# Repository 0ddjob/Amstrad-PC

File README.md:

# Amstrad PC Related Projects

## Amstrad ACL-386SX BIOS ROM
Dump of the ROM from the Amstrad ACL-386SX laptop computer.<br>
PhoenixBIOS A386 Version 1.01, dated 19-Apr-1990 (I think).<br>

## [Amstrad ACL-386SX External Floppy Adaptor](/Amstrad_ACL386_Floppy)
Small Centronics adaptor board to allow connection of a 3.5" floppy or Gotek (via IDC) or 5.25" floppy (via edge connector).<br>

### Status
11-Sep-2025: Work in progress<br>

## [Amstrad PPC XT CF-Lite](/Amstrad_PPC_Internal_Expansion)
An early attempt by an inexperienced me trying to replace the internal modem in the Amstrad PPC1512/1640 with a combination XT-IDE and CF-Lite board.<br>

It *should* work but I really need to re-visit the design (in light of several years more experience) and get this thing working!<br>

### Status
11-Sept-2025: Untested<br>

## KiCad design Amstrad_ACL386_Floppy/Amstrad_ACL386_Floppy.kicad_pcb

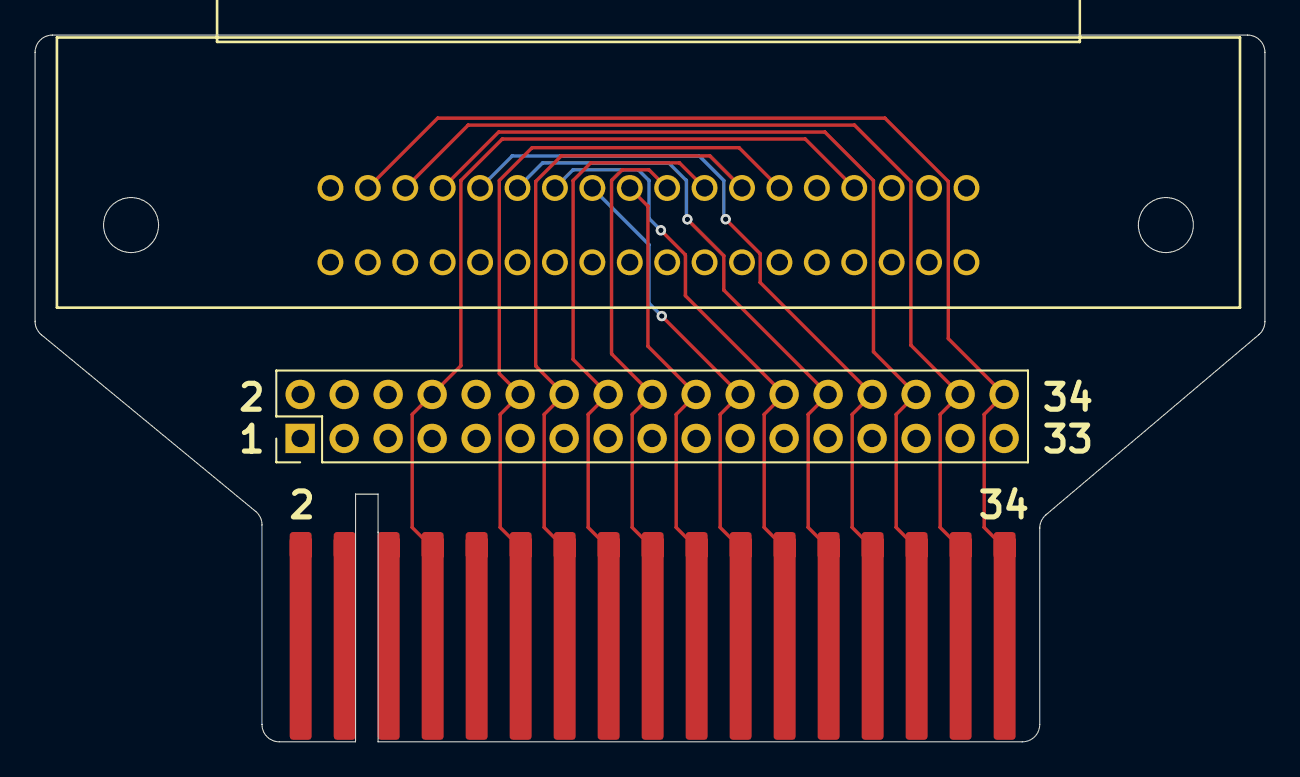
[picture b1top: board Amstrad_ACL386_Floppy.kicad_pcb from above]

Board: 2 copper layers, 71.0 x 40.8 mm, 3 parts (0 on the bottom side), 14 nets.

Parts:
J1: External Floppy; 112-036-113R001_Centronics_36way
J3: 3.5" Floppy; PinHeader_2x17_P2.54mm_Vertical
J4: 5.25" Floppy; 5.25_ Floppy Edge Connector

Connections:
DIR: J1.27, J3.18, J4.18
DSKCHG/RG: J1.35, J3.34, J4.34
GND: J1.1, J1.2, J1.3, J1.4, J1.5, J1.6, J1.7, J1.8, J1.9, J1.10, J1.11, J1.12, J1.13, J1.14, J1.15, J1.16, J1.17, J1.18, J1.36, J3.1, J3.3, J3.5, J3.7, J3.9, J3.11, J3.13, J3.15, J3.17, J3.19, J3.21, J3.23, J3.25, J3.27, J3.29, J3.31, J3.33, J4.1, J4.3, J4.5, J4.7, J4.9, J4.11, J4.13, J4.15, J4.17, J4.19, J4.21, J4.23, J4.25, J4.27, J4.29, J4.31, J4.33
HDSEL: J1.34, J3.32, J4.32
~DR0: J1.25, J3.14, J4.14
~DR1: J1.24, J3.12, J4.12
~INDEX: J1.22, J3.8, J4.8
~MTR1: J1.26, J3.16, J4.16
~RDATA: J1.33, J3.30, J4.30
~STEP: J1.28, J3.20, J4.20
~TRK0: J1.31, J3.26, J4.26
~WDATA: J1.29, J3.22, J4.22
~WGATE: J1.30, J3.24, J4.24
~WRTPRT: J1.32, J3.28, J4.28

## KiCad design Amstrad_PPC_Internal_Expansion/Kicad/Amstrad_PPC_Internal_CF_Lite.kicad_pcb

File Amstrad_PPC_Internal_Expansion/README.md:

# Amstrad PPC XT CF Lite
Internal CF interface for the Amstrad PPC512/640.<br>

Replaces the internal modem board with a combination ISA interface & XT-IDE/Compact Flash interface.<br> 

Heavily based on Sergey Kiselev's design<br>
[Github page](https://github.com/skiselev)<br>
[WWW page](http://www.malinov.com/Home/sergeys-projects/xt-cf-lite)<br>

Which is apparently a remake of James Pearce's card:<br>
[WWW page](http://www.lo-tech.co.uk/wiki/XT-CF-lite)<br>

I am using some of Sergey's Kicad symbols/footprints:<br>
[Sergey's Kicad symbols](https://github.com/skiselev/my_kicad_library)<br>

Changes requires for internal mounting in the Amstrad PPC:<br>
[1] The following signals are generated directly from the internal gate arrays and should be buffered with a non-inverting buffer (i.e. 72HC244): A00 to A07, !MEMW, !MEMR, !IOW, !IOR, RESET<br>
_(there are others but irrelevant for our purposes)_<br>
[2] The data signals (D0 to D7) are at CMOS levels and should be pulled up to TTL levels with 10KΩ resistors<br>
[3] The internal modem board we are replacing is roughly 200x120mm<br>
[4] Technically the PPC should be powered by the "expansion unit" and not the other way around ... don't tell anyone<br>

Currently untested ...<br><br>

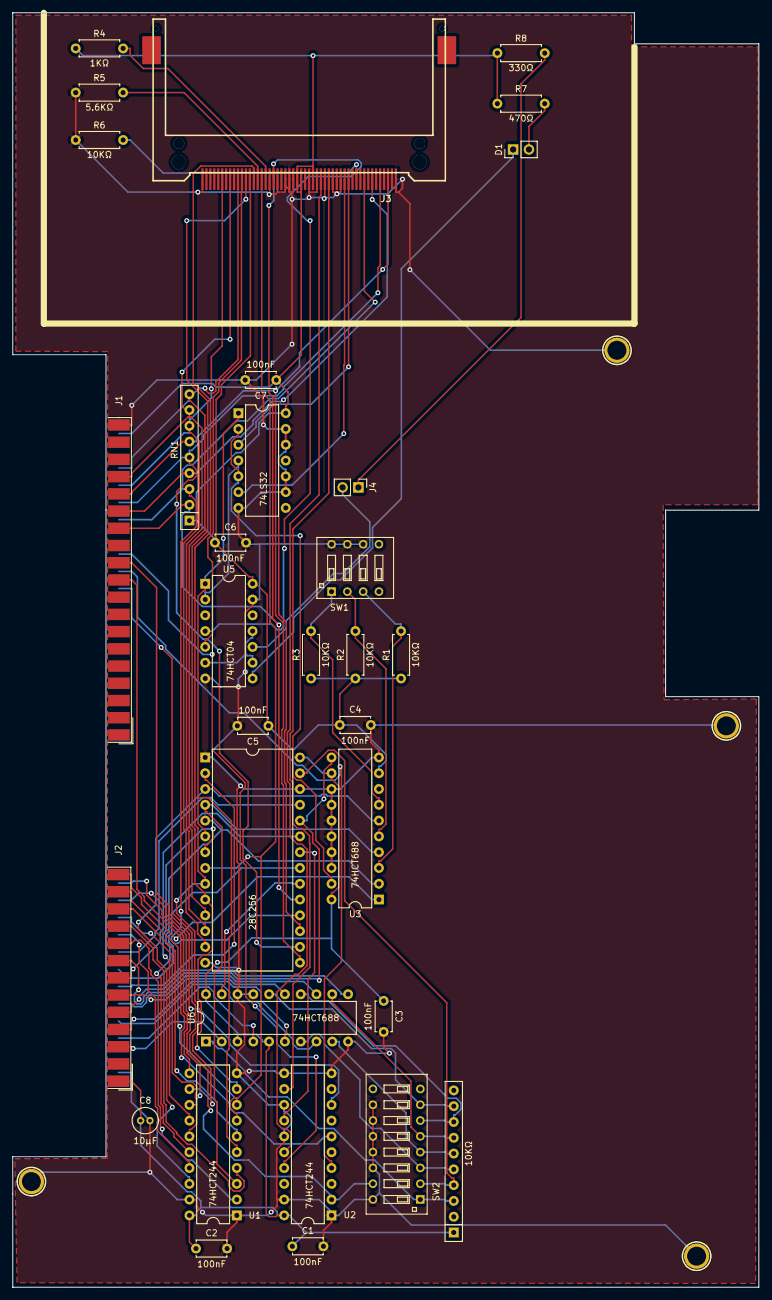
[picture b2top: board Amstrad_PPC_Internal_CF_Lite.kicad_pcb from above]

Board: 2 copper layers, 120.0 x 205.0 mm, 36 parts (0 on the bottom side), 71 nets.

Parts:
C1, C2, C3, C4, C5, C6, C7: 100nF; C_Disc_D4.7mm_W2.5mm_P5.00mm
C8: 10µF; C_Radial_D4.0mm_H5.0mm_P1.50mm
D1: LED; PinHeader_1x02_P2.54mm_Vertical
HOLE1, HOLE2, HOLE3, HOLE4: HOLE; Hole_3mm
J1: Amstrad_PPC_ISA_Connector_B; DSUB-37_Female_EdgeMount_P2.77mm
J2: Amstrad_PPC_ISA_Connector_A; DSUB-25_Female_EdgeMount_P2.77mm
J3: CONN_CF_CARD; Conn_CF_N7E50-Q516XX-40
J4: Conn_01x02; PinHeader_1x02_P2.54mm_Vertical
R1, R2, R3, R6: 10KΩ; R_Axial_DIN0207_L6.3mm_D2.5mm_P7.62mm_Horizontal
R4: 1KΩ; R_Axial_DIN0207_L6.3mm_D2.5mm_P7.62mm_Horizontal
R5: 5.6KΩ; R_Axial_DIN0207_L6.3mm_D2.5mm_P7.62mm_Horizontal
R7: 470Ω; R_Axial_DIN0207_L6.3mm_D2.5mm_P7.62mm_Horizontal
R8: 330Ω; R_Axial_DIN0207_L6.3mm_D2.5mm_P7.62mm_Horizontal
RN1: 10KΩ; R_Array_SIP9
RR1: 10KΩ; R_Array_SIP10
SW1: Switch_DIP_4_Positions
SW2: Switch_DIP_8_Positions
U1, U2: 74HCT244; DIP-20_W7.62mm
U3, U6: 74HCT688; DIP-20_W7.62mm
U4: 74LS32; DIP-14_W7.62mm
U5: 74HCT04; DIP-14_W7.62mm
U7: 28C256; DIP-28_W15.24mm

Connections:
/A00: J2.25 (A00), U1.11 (2A3)
/A01: J2.12 (A01), U1.8 (1A3)
/A02: J2.24 (A02), U1.13 (2A2)
/A03: J2.11 (A03), U1.6 (1A2)
/A04: J2.23 (A04), U1.15 (2A1)
/A05: J2.10 (A05), U1.4 (1A1)
/A06: J2.22 (A06), U1.17 (2A0)
/A07: J2.9 (A07), U1.2 (1A0)
/A08: J2.21 (A08), U7.25 (A8)
/A09: J2.8 (A09), U3.11 (P4), U7.24 (A9)
/A10: J2.20 (A10), U7.21 (A10)
/A11: J2.7 (A11), U7.23 (A11)
/A12: J2.19 (A12), U7.2 (A12)
/A13: J2.6 (A13), U6.15 (P6)
/A14: J2.18 (A14), U6.13 (P5)
/A15: J2.5 (A15), U6.11 (P4)
/A16: J2.17 (A16), U6.8 (P3)
/A17: J2.4 (A17), U6.6 (P2)
/A18: J2.16 (A18), U6.4 (P1)
/A19: J2.3 (A19), U6.2 (P0)
/AEN: J2.13 (AEN), U3.1 (G)
/B_A00: J3.20 (A0), U1.9 (2Y3), U7.10 (A0)
/B_A01: J3.19 (A1), U1.12 (1Y3), U7.9 (A1)
/B_A02: J3.18 (A2), U1.7 (2Y2), U7.8 (A2)
/B_A03: U1.14 (1Y2), U7.7 (A3)
/B_A04: U1.5 (2Y1), U4.1, U5.1, U7.6 (A4)
/B_A05: U1.16 (1Y1), U3.2 (P0), U7.5 (A5)
/B_A06: U1.3 (2Y0), U3.4 (P1), U7.4 (A6)
/B_A07: U1.18 (1Y0), U3.6 (P2), U7.3 (A7)
/CF_DMARQ: J3.43 (~INPACK), R5.2
/CF_IORDY: J3.42 (IORDY), R4.2
/D0: J1.35 (D0), J3.21 (D0), RN1.9 (R8), U7.11 (DQ0)
/D1: J1.16 (D1), J3.22 (D1), RN1.8 (R7), U7.12 (DQ1)
/D2: J1.34 (D2), J3.23 (D2), RN1.7 (R6), U7.13 (DQ2)
/D3: J1.15 (D3), J3.2 (D3), RN1.6 (R5), U7.15 (DQ3)
/D4: J1.33 (D4), J3.3 (D4), RN1.5 (R4), U7.16 (DQ4)
/D5: J1.14 (D5), J3.4 (D5), RN1.4 (R3), U7.17 (DQ5)
/D6: J1.32 (D6), J3.5 (D6), RN1.3 (R2), U7.18 (DQ6)
/D7: J1.13 (D7), J3.6 (D7), R6.2, RN1.2 (R1), U7.19 (DQ7)
/RESET: J1.30 (RESET), U2.17 (2A0)
/~B_IOR: J3.34 (~IORD), U2.12 (1Y3)
/~B_IOW: J3.35 (~IOWR), U2.16 (1Y1)
/~B_MEMR: U2.14 (1Y2), U7.22 (~OE)
/~CF_CS0: J3.7 (~CS0), U4.3
/~CF_CS1: J3.32 (~CS1), U4.6
/~CF_DASP: J3.45 (~DASP), U5.5
/~CF_RESET: J3.41 (~RESET), U5.4
/~IOR: J1.11 (~IOR), U2.8 (1A3)
/~IOW: J1.29 (~IOW), U2.4 (1A1)
/~MEMR: J1.10 (~MEMR), U2.6 (1A2)
/~MEMW: J1.28 (~MEMW), SW2.15, U2.2 (1A0)
/~ROMW: RR1.4, SW2.2, U7.27 (~WE)
/~ROM_CS: U6.19 (P=R), U7.20 (~CE)
GND: C1.2, C2.2, C3.2, C4.2, C5.2, C6.2, C7.2, C8.2, HOLE1.1, HOLE2.1, HOLE3.1, HOLE4.1, J1.19 (GND), J2.14 (GND), J3.1 (GND), J3.8 (A10), J3.9 (~ATASEL), J3.10 (A9), J3.11 (A8), J3.12 (A7), J3.14 (A6), J3.15 (A5), J3.16 (A4), J3.17 (A3), J3.39 (~CSEL), J3.50 (GND), R5.1, R6.1, SW1.6, SW1.7, SW1.8, SW2.10, SW2.11, SW2.12, SW2.13, SW2.14, SW2.16, U1.1 (1OE), U1.10 (GND), U1.19 (2OE), U2.1 (1OE), U2.10 (GND), U2.11 (2A3), U2.13 (2A2), U2.15 (2A1), U2.19 (2OE), U3.10 (GND), U3.13 (P5), U3.14 (R5), U3.15 (P6), U3.16 (R6), U3.17 (P7), U3.18 (R7), U4.7 (GND), U4.9, U4.10, U4.12, U4.13, U5.7 (GND), U5.13, U6.10 (GND), U6.17 (P7), U6.18 (R7), U7.1 (A14), U7.14 (GND), U7.26 (A13)
unnamed: D1.2 (A), R7.2
unnamed: D1.1 (K), U5.8
unnamed: J4.1, R8.2
unnamed: J4.2, U5.10
unnamed: U3.19 (P=R), U4.2, U4.5
unnamed: R1.2, SW1.3, U3.3 (R0)
unnamed: R2.2, SW1.2, U3.5 (R1)
unnamed: R3.2, SW1.1, U3.7 (R2)
unnamed: U4.4, U5.2
unnamed: U5.6, U5.9, U5.11
unnamed: RR1.3, SW2.1, U6.1 (G)
unnamed: RR1.5, SW2.3, U6.7 (R2)
unnamed: RR1.6, SW2.4, U6.9 (R3)
unnamed: RR1.7, SW2.5, U6.12 (R4)
unnamed: RR1.8, SW2.6, U6.14 (R5)
unnamed: RR1.9, SW2.7, U6.16 (R6)
VCC: C1.1, C2.1, C3.1, C4.1, C5.1, C6.1, C7.1, C8.1, J1.37 (VCC), J2.1 (+5V), J3.13 (VCC), J3.36 (~WE), J3.38 (VCC), J3.44 (~REG), R1.1, R2.1, R3.1, R4.1, R7.1, R8.1, RN1.1 (common), RR1.1 (COM), U1.20 (VCC), U2.20 (VCC), U3.9 (R3), U3.12 (R4), U3.20 (VCC), U4.14 (VCC), U5.14 (VCC), U6.3 (R0), U6.5 (R1), U6.20 (VCC), U7.28 (VCC)

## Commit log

2025-09-11 Reorganising Amstrad PC projects
2025-09-11 Initial commit of ACL-386 files
2025-09-11 Removed backgrounds
2025-09-12 PCB tweaks
2025-09-21 Configured ROM image
2025-09-21 From boot floppy
